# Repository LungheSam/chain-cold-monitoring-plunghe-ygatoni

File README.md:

# IoT-Based Cold Chain Monitoring for Vaccine Storage Units

CMU Africa · 04-645 A Internet of Things · Fall 2026
Putshu Lunghe Samuel (plunghe) · Yves Dominique Gatoni (ygatoni)

A Raspberry Pi 4 node watches a vaccine fridge (+2 to +8 °C): internal and ambient temperature,
humidity, door and 12 V power. It raises a local alarm and an SMS, keeps a record of every
temperature excursion, and is exposed as a W3C **Web Thing**. A React dashboard shows live data,
history and analytics. Extension: keypad PIN, solenoid lock and a QR unlock page.

```
edge (Pi) ──MQTT/TLS──> EMQX Cloud ──> back end (Railway: Node.js, WoT TD, SSE) ──> Firestore
                                               │                                     │
                                               └──> Africa's Talking SMS              └──> dashboard (Railway: React)
```

See [docs/architecture.md](docs/architecture.md) for the full picture.

## Where it runs

| Part | Service | Guide |
|---|---|---|
| MQTT broker | EMQX Cloud Serverless (free, TLS 8883) | [docs/deploy-railway.md](docs/deploy-railway.md) step 1 |
| Back end | Railway (service 1, root `backend/`) | [docs/deploy-railway.md](docs/deploy-railway.md) |
| Dashboard + unlock page | Railway (service 2, root `frontend/`) | [docs/deploy-railway.md](docs/deploy-railway.md) |
| Database + sign-in | Firebase (Firestore + Authentication) | [docs/firebase-setup.md](docs/firebase-setup.md) |
| SMS | Africa's Talking | [backend/README.md](backend/README.md) |

Why these choices (and why not HiveMQ or Firebase Hosting): [docs/decisions.md](docs/decisions.md) D3, D4, D18.

## Repository layout

| Folder | Contents |
|---|---|
| [edge/](edge/) | Python firmware for the Pi (alarm logic, drivers, keypad and lock, mock mode, offline queue) |
| [backend/](backend/) | Node.js back end: MQTT ingest, Web Thing API, Firestore, SMS, local test broker |
| [frontend/](frontend/) | React dashboard (light/dark), QR unlock page, small server for Railway |
| [firebase/](firebase/) | Firestore security rules and indexes |
| [broker/](broker/) | Mosquitto configuration (Docker), kept as a fallback broker |
| [hardware/](hardware/) | Fritzing wiring list, FreeCAD enclosure, KiCad carrier PCB |
| [docs/](docs/) | Architecture, wiring, MQTT topics, Thing Description, data model, decisions, [components list](docs/components.md), [purchase request](docs/purchase-request.md) ([Excel](docs/purchase-request.xlsx)), [test plan](docs/test-plan.md), [demo script](docs/demo-script.md), [report pictures](docs/report-media.md) |

## Prerequisites

| Tool | For | Notes |
|---|---|---|
| Python 3.11+ | edge | on the Pi it comes with Raspberry Pi OS |
| Node.js 24 LTS | backend, frontend | |
| FreeCAD 1.1, KiCad 10, Fritzing | hardware | FreeCAD and KiCad are not on PATH (paths in docs/decisions.md) |

Docker is not needed: `npm run broker` gives a local MQTT broker for testing.

## Running it on a laptop

Secrets go in `.env` files that are never committed. Each part has a `.env.example` to copy:
`backend/.env`, `edge/.env`, `frontend/.env.local`.

**First time:**

```bash
cd backend && npm install && npm test
cd ../frontend && npm install && npm test
cd ../edge && python -m venv .venv && .venv/Scripts/pip install -r requirements.txt && .venv/Scripts/python -m pytest
```

**Without any account** (memory store, local broker, demo dashboard):

```bash
cd backend && npm run broker       # terminal 1: local MQTT broker
cd backend && npm run dev          # terminal 2: back end (STORE=memory, DEV_AUTH=1 in backend/.env)
cd edge && .venv/Scripts/python -m coldchain.node    # terminal 3: simulated fridge (type `help`)
cd frontend && npm run demo        # terminal 4: dashboard with a generated week of data
```

**With the real services** (Firebase, EMQX: `backend/.env`, `edge/.env` and `frontend/.env.local` filled in):

```bash
cd backend && npm run check        # tests both MQTT logins and Firestore, prints no secrets
cd backend && npm run dev          # http://localhost:8080
cd edge && .venv/Scripts/python -m coldchain.node
cd frontend && npm run dev         # http://localhost:5173
```

In the node's terminal, `temp 9.5` makes the fridge too warm: WARNING at once, ALARM after 20 s.
More: [edge/README.md](edge/README.md), [backend/README.md](backend/README.md), [frontend/README.md](frontend/README.md).
On the Pi: [edge/SETUP.md](edge/SETUP.md).

**Whole chain in one command** (in-process broker + back end + simulated node, 34 checks):

```bash
cd backend && npm run e2e
```

## Project phases

| Phase | Content | Status |
|---|---|---|
| 0 | Plan and skeleton | done |
| 1 | Alarm logic + simulator | done |
| 2 | Real edge drivers, bring-up, Fritzing wiring list | done (not yet run on the Pi) |
| 3 | Back end (MQTT, Firestore, WoT, SMS, auth) | done, running against the real Firestore and EMQX |
| 4 | Dashboard + seed data | done, running against Firebase; light and dark themes |
| 5 | Keypad, lock, QR unlock | done (mock keypad and lock; not yet on the Pi) |
| 6 | FreeCAD enclosure | done (script runs headless, all parts valid; dimensions to VERIFY before printing) |
| 7 | KiCad carrier PCB | done (ERC/DRC clean, Gerbers ready; header position and parts to VERIFY before ordering) |
| 8 | End-to-end tests and demo script | done (`npm run e2e`: 34/34; system tests on the Pi to do, see docs/test-plan.md) |

Next: deploy on Railway ([docs/deploy-railway.md](docs/deploy-railway.md)), then the Pi bring-up.

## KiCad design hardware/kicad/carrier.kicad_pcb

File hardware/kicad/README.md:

# Carrier PCB (KiCad 10)

A 2-layer board the size of a Raspberry Pi HAT (65 × 56.5 mm) that plugs onto the Pi's 40-pin header
and replaces the breadboard wiring of `docs/wiring.md`. It is fully generated by scripts from one
table, checked by KiCad, and exported ready to order.

```bash
cd hardware/kicad
./build.sh          # about 2.5 minutes; needs KiCad 10 (its own Python and kicad-cli)
```

| File | What it does |
|---|---|
| `carrier.py` | **The netlist table**: every part, value, footprint and the net of each pin. Change the circuit here. |
| `make_schematic.py` | Writes `carrier.kicad_sch`: symbols copied from KiCad's library, a net label on every pin, functional blocks |
| `make_pcb.py` | Writes `carrier.kicad_pcb`: placement table, board outline, routing, GND pour on both layers, silkscreen labels |
| `router.py` | Small A* maze router (KiCad has no autorouter, and Freerouting needs Java) |
| `carrier.kicad_dru` | Extra design rules: lock tracks at least 1.0 mm |
| `build.sh` | Runs everything: ERC, routing, DRC (with schematic parity), exports |
| `output/` | Schematic PDF, ERC/DRC reports, `carrier-gerbers.zip` (Gerbers + drill), BOM, pick-and-place, STEP, renders |

The `.kicad_sch` and `.kicad_pcb` open normally in KiCad. If you edit them by hand, the next
`./build.sh` overwrites them: make the change in `carrier.py` or the placement table instead.

## Checks (last build)

- ERC: 0 errors, 0 warnings.
- DRC: 0 errors, 0 unconnected pads, schematic parity OK (every footprint, value and net matches the
  schematic). 5 warnings, all silkscreen text touching other silkscreen.

## What is on the board

| Block | Parts | Notes |
|---|---|---|
| Pi header | J1 2×20 female socket on the **bottom** side | Pin 1 = square pad, matches the Pi when the board sits on top |
| DS18B20 | J2 (JST-XH 3), R1 4.7 kΩ to 3.3 V | 1-Wire pull-up |
| DHT22 | J3 (JST-XH 3), R2 10 kΩ | leave R2 out if the DHT22 module has its own pull-up (VERIFY) |
| Reed switch | J4 (JST-XH 2) | uses the Pi's internal pull-up |
| 12 V sense | J9 (screw), R3 10 kΩ / R4 2.7 kΩ divider, C1 100 nF, R5 1 kΩ, D1 BAT54S | 2.55 V at 12 V, 3.19 V at 15 V; BAT54S clamps GPIO 22 between GND and 3.3 V |
| Buzzer | J6, R6 1 kΩ, Q1 BC547, D2 1N4148 | low-side switch, diode across the coil |
| LEDs | J5, R7/R8 330 Ω | LEDs sit on the lid; common GND |
| Lock | J10 (5 V lock adapter in), J11 (solenoid), Q2 AO3400A, R9 100 Ω, R10 10 kΩ, D3 1N4007 | R10 holds the gate low, so the lock is OFF when the Pi is off or booting |
| LCD level shifter | Q3/Q4 BSS138, R11/R12 10 kΩ to 5 V, J7 (JST-XH 4, backpack order GND 5V SDA SCL) | the 3.3 V side uses the Pi's own 1.8 kΩ pull-ups |
| Keypad, spare | J8 (1×8 header), J12 (GPIO 26 + GND) | |

Refs match the breadboard parts list in `docs/wiring.md` where the part is the same.
Differences from the breadboard, and why:

- **Q2 is an AO3400A (SOT-23)** instead of the IRLB8721 (TO-220). It is fully on at 3.3 V gate drive
  (R_DS(on) below 50 mΩ at 2.5 V, datasheet), so at about 1 A it dissipates about 50 mW. The TO-220 laid flat
  would need 21 × 11 mm of board.
- **D1 is a BAT54S** (two Schottky diodes in one package) instead of a single 1N5819: it clamps
  both above 3.3 V and below GND.
- **The BSS138 level shifter is on the board** instead of the separate module (D13).

### Why no PC817 optocoupler on the 12 V sense input

An optocoupler isolates two circuits with different grounds. Here the 12 V adapter's negative
must already be joined to the Pi's GND: the lock and the sense divider need a common ground anyway.
So isolation would gain nothing, and the divider + series resistor + clamp is simpler and protects
the GPIO against the realistic faults (a 15 V unloaded adapter, spikes, reversed or missing
ground on the sense wire). A PC817 would be the right choice only if the sensed supply had its own
ground, for example a separate battery system. It would then work like this: 12 V → resistor →
PC817 LED, and the photo-transistor pulls GPIO 22 low against a pull-up, so the logic is inverted.
Nothing on this board ever connects to 230 V.

### Track widths

| Nets | Width | Why |
|---|---|---|
| `+5V_LOCK`, `LOCK_N`, lock return (J10 GND ↔ Q2) | 1.0 mm | solenoid current about 1 A (VERIFY). IPC-2221 for 1 oz outer copper and a 10 °C rise needs 0.30 mm; 1.0 mm leaves margin for the pull-in surge |
| `+5V` | 0.4 mm | buzzer, LCD backlight (well under 0.5 A) |
| `+3V3`, `GND` tracks | 0.3 mm | plus a GND pour on both layers |
| signals | 0.25 mm | |

The Peltier's 12 V / ~5 A never comes onto this board: J9 carries only the divider's ~1 mA.

## Ordering

Upload `output/carrier-gerbers.zip` to any 2-layer PCB service (for example JLCPCB, PCBWay):
1.6 mm FR-4, 1 oz copper, HASL or ENIG, any colour. The design uses 0.25 mm tracks, 0.2 mm
clearance and 0.3 mm via drills, which every standard process allows. `output/carrier-bom.csv`
lists the parts and `output/carrier-pos.csv` the SMD positions (origin: bottom-left corner).

Shipping from abroad will not arrive before the 2 Dec demo (decisions.md), so the demo uses the
breadboard/protoboard build and this design is shown in the report.

## Before ordering: VERIFY

- [ ] Pi header position and pin 1 (from the HAT drawing: rows 2.23 / 4.77 mm from the top edge,
      pin 1 at x = 8.37 mm): print `output/carrier-top.png` at 1:1 or check the PDF against the Pi
- [ ] Standoff height between Pi and board: about 11 mm for an 8.5 mm female socket (measure the socket)
- [ ] BC547 pin order C-B-E (the footprint uses this order)
- [x] Keypad ribbon order R1–R4, C1–C4 matches J8 pins 1–8 (seller's diagram)
- [ ] LCD backpack pull-ups: if it already has 5 V pull-ups, leave out R11/R12
- [ ] DHT22 module pull-up: if it has one, leave out R2
- [ ] Solenoid current (measure): if it is above 1.5 A, ask for wider tracks

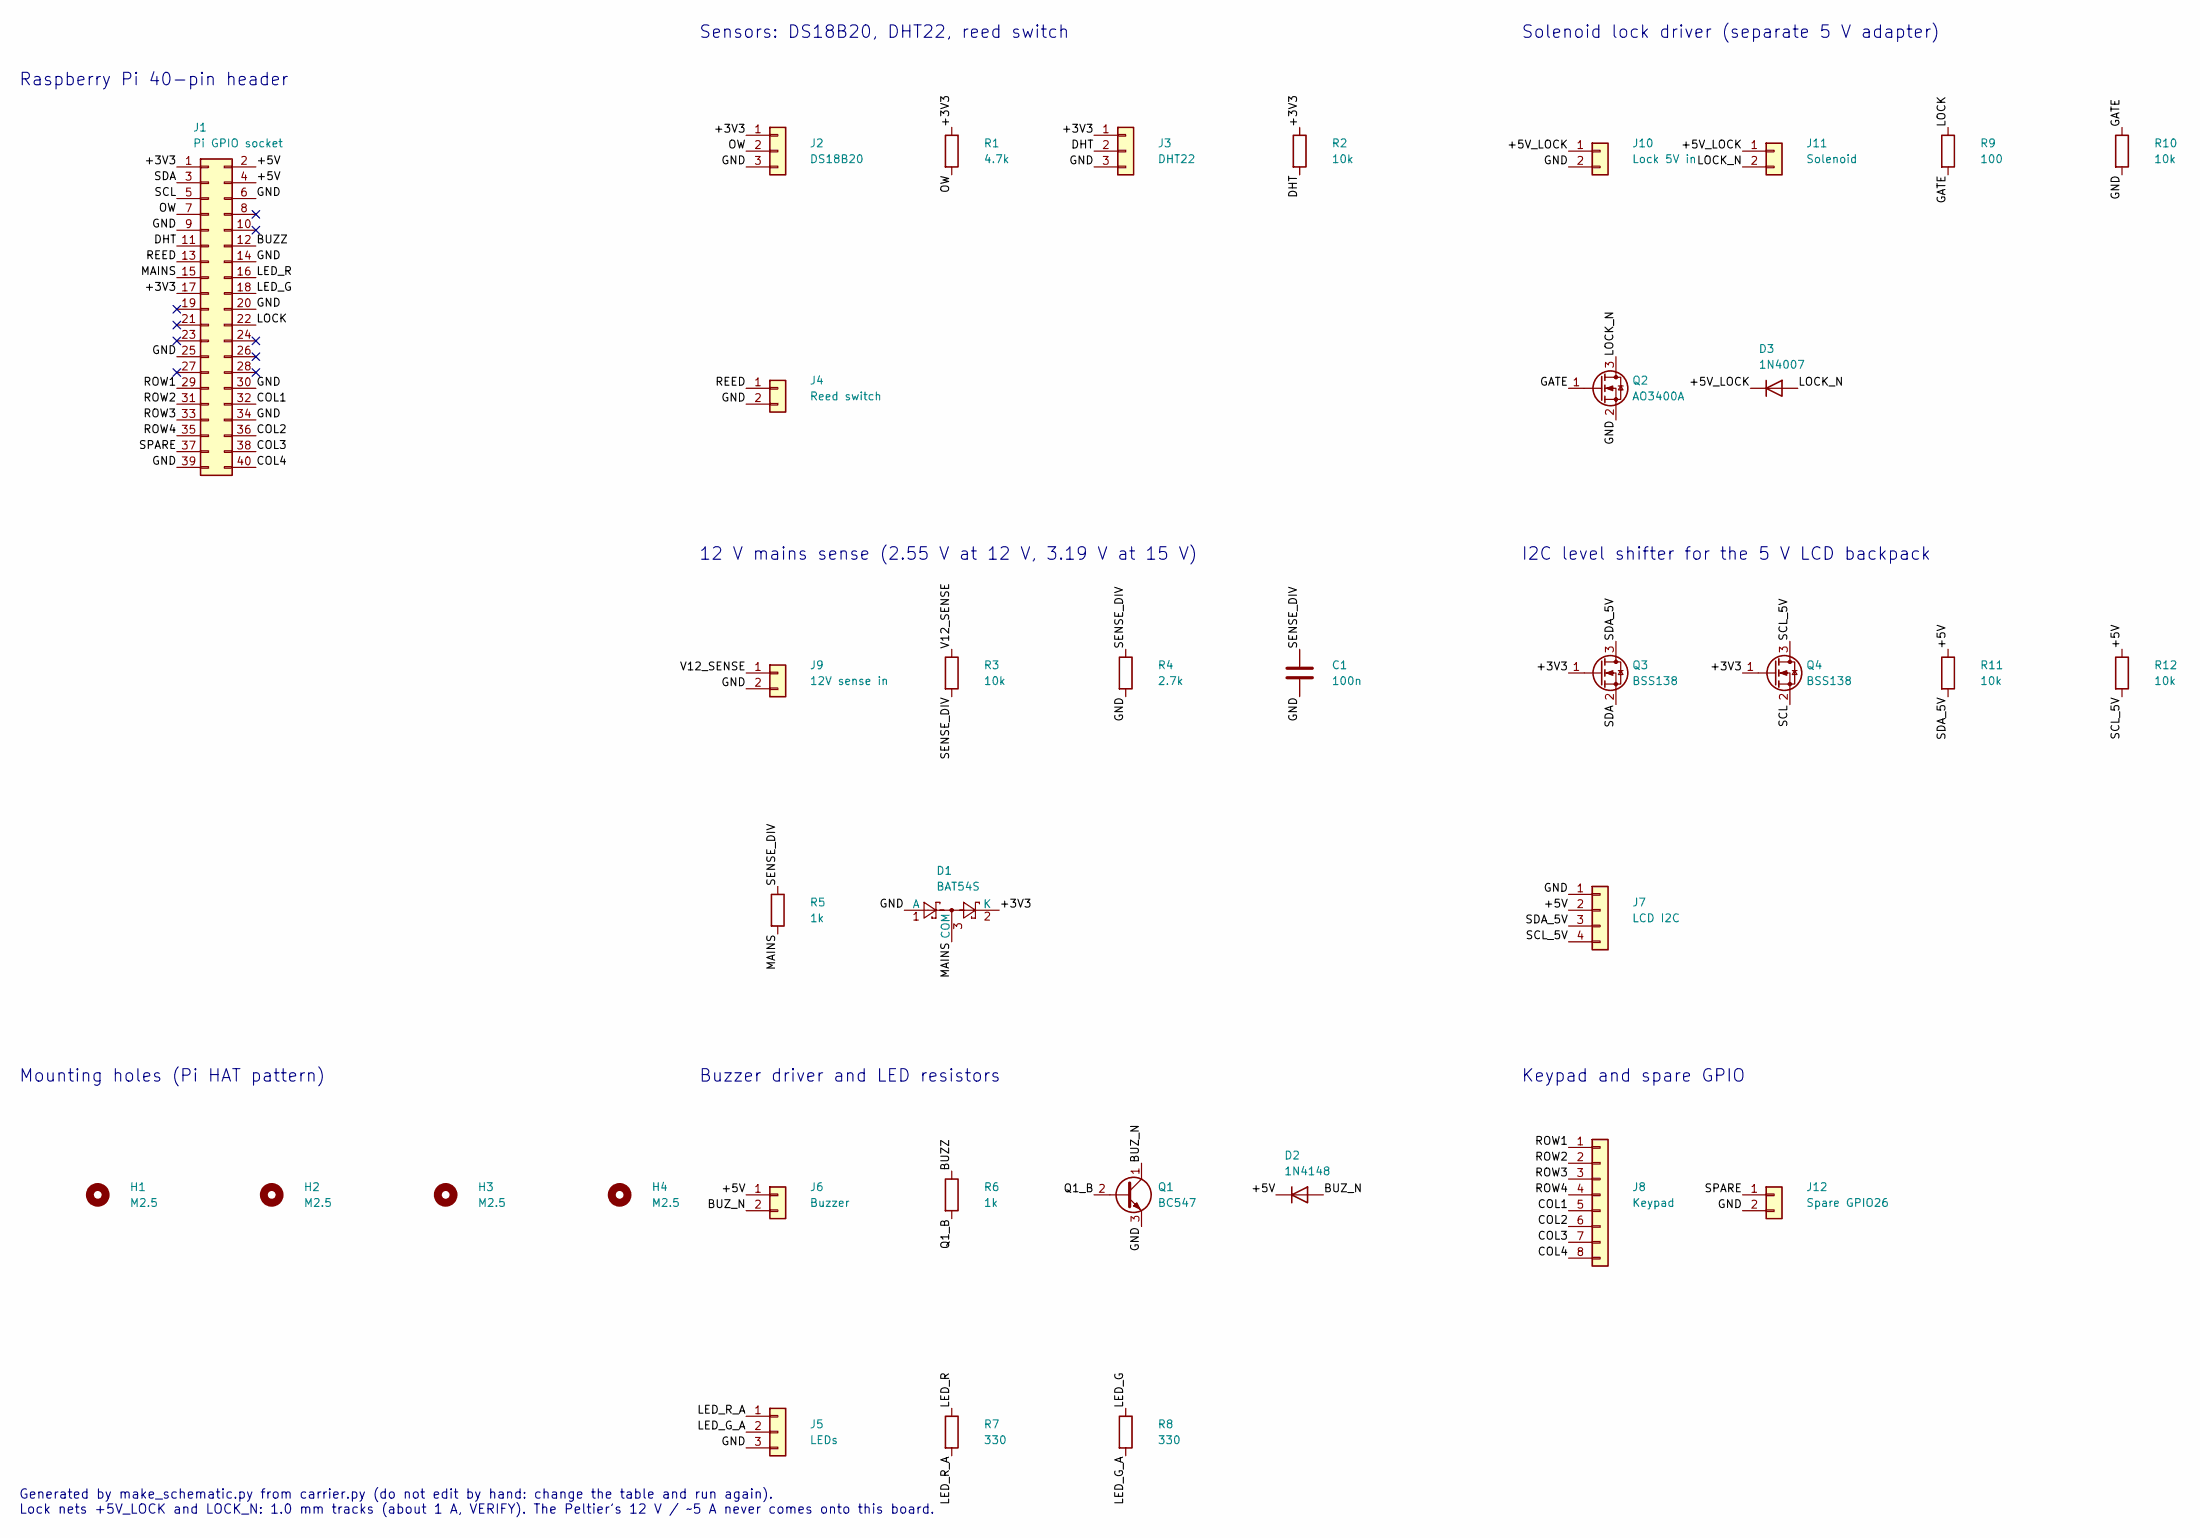
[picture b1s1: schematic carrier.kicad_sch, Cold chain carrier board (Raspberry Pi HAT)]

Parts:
C1: 100n; C_Disc_D5.0mm_W2.5mm_P5.00mm
D1: BAT54S; SOT-23
D2: 1N4148; D_DO-35_SOD27_P7.62mm_Horizontal
D3: 1N4007; D_DO-41_SOD81_P10.16mm_Horizontal
H1, H2, H3, H4: M2.5; MountingHole_2.7mm_M2.5
J1: Pi GPIO socket; PinSocket_2x20_P2.54mm_Vertical
J2: DS18B20; JST_XH_B3B-XH-A_1x03_P2.50mm_Vertical
J3: DHT22; JST_XH_B3B-XH-A_1x03_P2.50mm_Vertical
J4: Reed switch; JST_XH_B2B-XH-A_1x02_P2.50mm_Vertical
J5: LEDs; JST_XH_B3B-XH-A_1x03_P2.50mm_Vertical
J6: Buzzer; JST_XH_B2B-XH-A_1x02_P2.50mm_Vertical
J7: LCD I2C; JST_XH_B4B-XH-A_1x04_P2.50mm_Vertical
J8: Keypad; PinHeader_1x08_P2.54mm_Vertical
J9: 12V sense in; TerminalBlock_Phoenix_MKDS-1,5-2-5.08_1x02_P5.08mm_Horizont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
J10: Lock 5V in; TerminalBlock_Phoenix_MKDS-1,5-2-5.08_1x02_P5.08mm_Horizont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
J11: Solenoid; TerminalBlock_Phoenix_MKDS-1,5-2-5.08_1x02_P5.08mm_Horizont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
J12: Spare GPIO26; PinHeader_1x02_P2.54mm_Vertical
Q1: BC547; TO-92_Inline
Q2: AO3400A; SOT-23
Q3, Q4: BSS138; SOT-23
R1: 4.7k; R_Axial_DIN0207_L6.3mm_D2.5mm_P7.62mm_Horizontal
R2, R3, R10, R11, R12: 10k; R_Axial_DIN0207_L6.3mm_D2.5mm_P7.62mm_Horizontal
R4: 2.7k; R_Axial_DIN0207_L6.3mm_D2.5mm_P7.62mm_Horizontal
R5, R6: 1k; R_Axial_DIN0207_L6.3mm_D2.5mm_P7.62mm_Horizontal
R7, R8: 330; R_Axial_DIN0207_L6.3mm_D2.5mm_P7.62mm_Horizontal
R9: 100; R_Axial_DIN0207_L6.3mm_D2.5mm_P7.62mm_Horizontal

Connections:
/+3V3: D1.2 (K), J1.1, J1.17, J2.1, J3.1, Q3.1 (G), Q4.1 (G), R1.1, R2.1
/+5V: D2.1 (K), J1.2, J1.4, J6.1, J7.2, R11.1, R12.1
/+5V_LOCK: D3.1 (K), J10.1, J11.1
/BUZZ: J1.12, R6.1
/BUZ_N: D2.2 (A), J6.2, Q1.1 (C)
/COL1: J1.32, J8.5
/COL2: J1.36, J8.6
/COL3: J1.38, J8.7
/COL4: J1.40, J8.8
/DHT: J1.11, J3.2, R2.2
/GATE: Q2.1 (G), R9.2, R10.1
/GND: C1.2, D1.1 (A), J1.6, J1.9, J1.14, J1.20, J1.25, J1.30, J1.34, J1.39, J2.3, J3.3, J4.2, J5.3, J7.1, J9.2, J10.2, J12.2, Q1.3 (E), Q2.2 (S), R4.2, R10.2
/LED_G: J1.18, R8.1
/LED_G_A: J5.2, R8.2
/LED_R: J1.16, R7.1
/LED_R_A: J5.1, R7.2
/LOCK: J1.22, R9.1
/LOCK_N: D3.2 (A), J11.2, Q2.3 (D)
/MAINS: D1.3 (COM), J1.15, R5.2
/OW: J1.7, J2.2, R1.2
/Q1_B: Q1.2 (B), R6.2
/REED: J1.13, J4.1
/ROW1: J1.29, J8.1
/ROW2: J1.31, J8.2
/ROW3: J1.33, J8.3
/ROW4: J1.35, J8.4
/SCL: J1.5, Q4.2 (S)
/SCL_5V: J7.4, Q4.3 (D), R12.2
/SDA: J1.3, Q3.2 (S)
/SDA_5V: J7.3, Q3.3 (D), R11.2
/SENSE_DIV: C1.1, R3.2, R4.1, R5.1
/SPARE: J1.37, J12.1
/V12_SENSE: J9.1, R3.1

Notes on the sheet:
Raspberry Pi 40-pin header
Sensors: DS18B20, DHT22, reed switch
12 V mains sense (2.55 V at 12 V, 3.19 V at 15 V)
Buzzer driver and LED resistors
Solenoid lock driver (separate 5 V adapter)
I2C level shifter for the 5 V LCD backpack
Keypad and spare GPIO
Mounting holes (Pi HAT pattern)
Generated by make_schematic.py from carrier.py (do not edit by hand: change the table and run again). Lock nets +5V_LOCK and LOCK_N: 1.0 mm tracks (about 1 A, VERIFY). The Peltier's 12 V / ~5 A never comes onto this board.

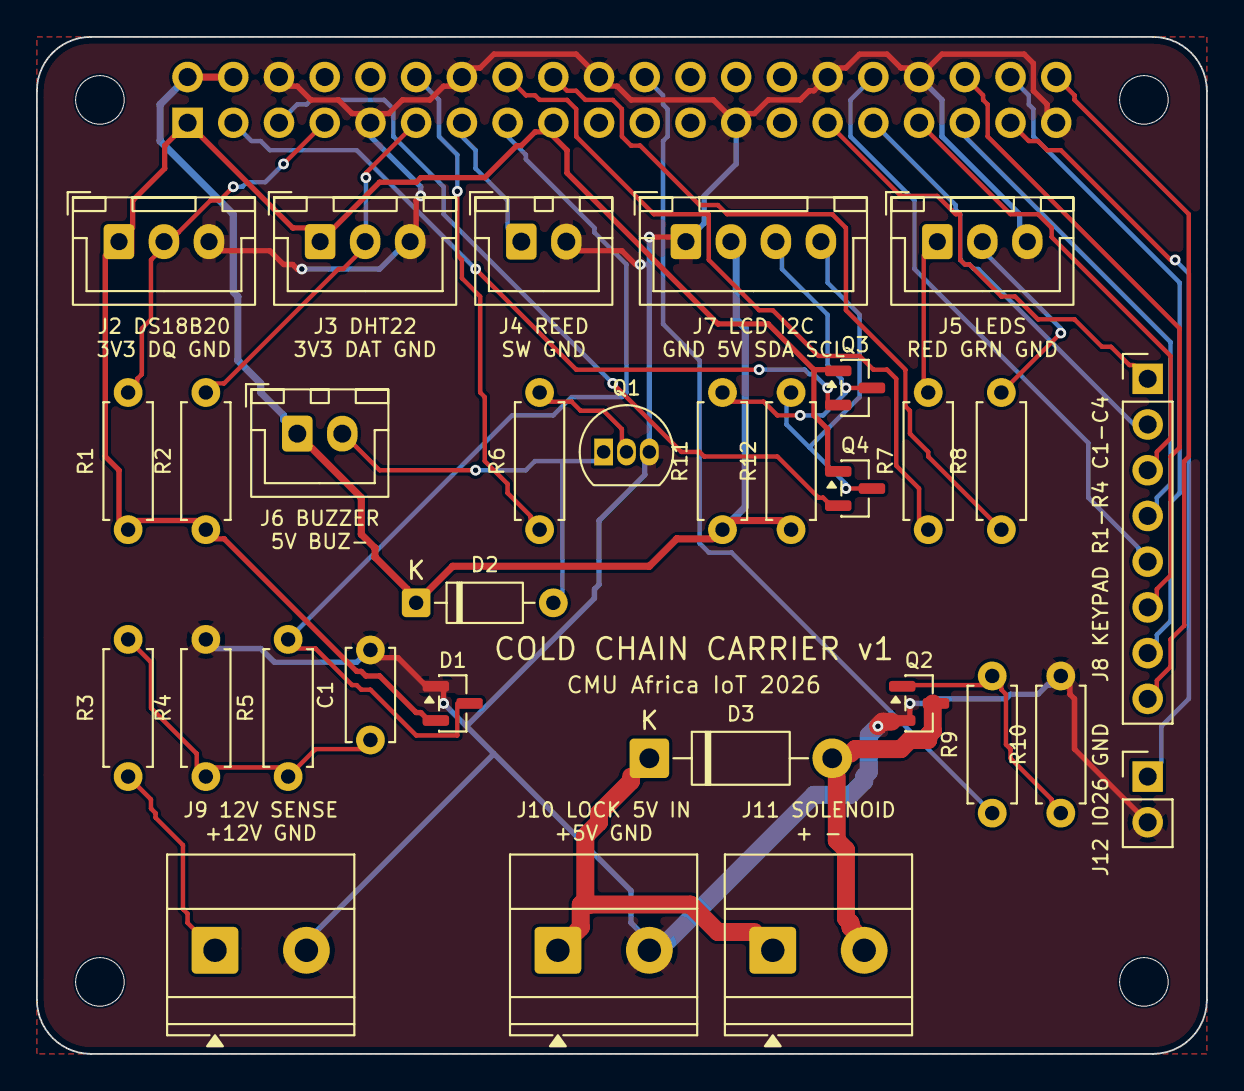
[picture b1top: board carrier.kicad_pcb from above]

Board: 2 copper layers, 65.0 x 56.5 mm, 36 parts (1 on the bottom side), 33 nets.

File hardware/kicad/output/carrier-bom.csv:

"Refs","Value","Footprint","Qty","Notes"
"C1","100n","Capacitor_THT:C_Disc_D5.0mm_W2.5mm_P5.00mm","1","filters noise on the sense line"
"D1","BAT54S","Package_TO_SOT_SMD:SOT-23","1","clamps GPIO 22 between GND and 3.3 V"
"D2","1N4148","Diode_THT:D_DO-35_SOD27_P7.62mm_Horizontal","1","across the buzzer coil"
"D3","1N4007","Diode_THT:D_DO-41_SOD81_P10.16mm_Horizontal","1","flyback diode across the solenoid"
"J1","Pi GPIO socket","Connector_PinSocket_2.54mm:PinSocket_2x20_P2.54mm_Vertical","1","2x20 female socket on the bottom side"
"J2","DS18B20","Connector_JST:JST_XH_B3B-XH-A_1x03_P2.50mm_Vertical","1",""
"J3","DHT22","Connector_JST:JST_XH_B3B-XH-A_1x03_P2.50mm_Vertical","1",""
"J4","Reed switch","Connector_JST:JST_XH_B2B-XH-A_1x02_P2.50mm_Vertical","1","uses the Pi's internal pull-up"
"J5","LEDs","Connector_JST:JST_XH_B3B-XH-A_1x03_P2.50mm_Vertical","1",""
"J6","Buzzer","Connector_JST:JST_XH_B2B-XH-A_1x02_P2.50mm_Vertical","1",""
"J7","LCD I2C","Connector_JST:JST_XH_B4B-XH-A_1x04_P2.50mm_Vertical","1","same order as the PCF8574 backpack"
"J8","Keypad","Connector_PinHeader_2.54mm:PinHeader_1x08_P2.54mm_Vertical","1","ribbon R1 R2 R3 R4 C1 C2 C3 C4, left to right with the keys facing you"
"J9","12V sense in","TerminalBlock_Phoenix:TerminalBlock_Phoenix_MKDS-1,5-2-5.08_1x02_P5.08mm_Horizontal","1","only the divider's ~1 mA; never the Peltier current"
"J10","Lock 5V in","TerminalBlock_Phoenix:TerminalBlock_Phoenix_MKDS-1,5-2-5.08_1x02_P5.08mm_Horizontal","1","separate 5 V 2 A adapter; its GND joins the Pi GND here"
"J11","Solenoid","TerminalBlock_Phoenix:TerminalBlock_Phoenix_MKDS-1,5-2-5.08_1x02_P5.08mm_Horizontal","1",""
"J12","Spare GPIO26","Connector_PinHeader_2.54mm:PinHeader_1x02_P2.54mm_Vertical","1",""
"Q1","BC547","Package_TO_SOT_THT:TO-92_Inline","1","C-B-E pin order (VERIFY on the part)"
"Q2","AO3400A","Package_TO_SOT_SMD:SOT-23","1","logic-level at 3.3 V, 5.7 A; the breadboard uses an IRLB8721 instead (docs/wiring.md)"
"Q3,Q4","BSS138","Package_TO_SOT_SMD:SOT-23","2",""
"R1","4.7k","Resistor_THT:R_Axial_DIN0207_L6.3mm_D2.5mm_P7.62mm_Horizontal","1","1-Wire pull-up"
"R2,R3,R10,R11,R12","10k","Resistor_THT:R_Axial_DIN0207_L6.3mm_D2.5mm_P7.62mm_Horizontal","5","5 V side pull-up; the 3.3 V side uses the Pi's own 1.8k pull-ups,DHT22 pull-up; leave out if the module has one (VERIFY),keeps the lock OFF when the Pi is off"
"R4","2.7k","Resistor_THT:R_Axial_DIN0207_L6.3mm_D2.5mm_P7.62mm_Horizontal","1",""
"R5,R6","1k","Resistor_THT:R_Axial_DIN0207_L6.3mm_D2.5mm_P7.62mm_Horizontal","2","limits the clamp current"
"R7,R8","330","Resistor_THT:R_Axial_DIN0207_L6.3mm_D2.5mm_P7.62mm_Horizontal","2","green LED,red LED"
"R9","100","Resistor_THT:R_Axial_DIN0207_L6.3mm_D2.5mm_P7.62mm_Horizontal","1","gate series resistor"

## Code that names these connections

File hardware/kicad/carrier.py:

"""The carrier board as a table: every part, its value, footprint and which net each pin is on.

make_schematic.py and make_pcb.py both read this table, so the schematic and the board can never
disagree (and `kicad-cli pcb drc --schematic-parity` checks it again).

Circuit decisions are in docs/wiring.md. Pin numbers of the Pi header are physical pin numbers.
"""

# ---------------------------------------------------------------- Raspberry Pi 40-pin header
# Physical pin -> net. Pins that are not listed are not used (no-connect flags in the schematic).
PI_PINS = {
    1: "+3V3", 17: "+3V3",
    2: "+5V", 4: "+5V",
    6: "GND", 9: "GND", 14: "GND", 20: "GND", 25: "GND", 30: "GND", 34: "GND", 39: "GND",
    3: "SDA",        # GPIO 2
    5: "SCL",        # GPIO 3
    7: "OW",         # GPIO 4   DS18B20 (1-Wire)
    11: "DHT",       # GPIO 17  DHT22
    12: "BUZZ",      # GPIO 18  buzzer (PWM)
    13: "REED",      # GPIO 27  door reed switch (internal pull-up)
    15: "MAINS",     # GPIO 22  12 V present (divider)
    16: "LED_R",     # GPIO 23
    18: "LED_G",     # GPIO 24
    22: "LOCK",      # GPIO 25  lock MOSFET gate (pulled down at boot)
    29: "ROW1", 31: "ROW2", 33: "ROW3", 35: "ROW4",   # GPIO 5, 6, 13, 19
    32: "COL1", 36: "COL2", 38: "COL3", 40: "COL4",   # GPIO 12, 16, 20, 21
    37: "SPARE",     # GPIO 26  kept free (e.g. a hardware acknowledge button)
}

# Footprint shortcuts
JST2 = "Connector_JST:JST_XH_B2B-XH-A_1x02_P2.50mm_Vertical"
JST3 = "Connector_JST:JST_XH_B3B-XH-A_1x03_P2.50mm_Vertical"
JST4 = "Connector_JST:JST_XH_B4B-XH-A_1x04_P2.50mm_Vertical"
SCREW2 = "TerminalBlock_Phoenix:TerminalBlock_Phoenix_MKDS-1,5-2-5.08_1x02_P5.08mm_Horizontal"
RES = "Resistor_THT:R_Axial_DIN0207_L6.3mm_D2.5mm_P7.62mm_Horizontal"

# ---------------------------------------------------------------- parts
# ref: (symbol, value, footprint, {pin number: net}, group, note)
PARTS = {
    "J1": ("Connector_Generic:Conn_02x20_Odd_Even", "Pi GPIO socket",
           "Connector_PinSocket_2.54mm:PinSocket_2x20_P2.54mm_Vertical",
           {str(p): n for p, n in PI_PINS.items()}, "pi", "2x20 female socket on the bottom side"),

    # Sensors
    "J2": ("Connector_Generic:Conn_01x03", "DS18B20", JST3, {"1": "+3V3", "2": "OW", "3": "GND"}, "sensors", ""),
    "R1": ("Device:R", "4.7k", RES, {"1": "+3V3", "2": "OW"}, "sensors", "1-Wire pull-up"),
    "J3": ("Connector_Generic:Conn_01x03", "DHT22", JST3, {"1": "+3V3", "2": "DHT", "3": "GND"}, "sensors", ""),
    "R2": ("Device:R", "10k", RES, {"1": "+3V3", "2": "DHT"}, "sensors",
           "DHT22 pull-up; leave out if the module has one (VERIFY)"),
    "J4": ("Connector_Generic:Conn_01x02", "Reed switch", JST2, {"1": "REED", "2": "GND"}, "sensors",
           "uses the Pi's internal pull-up"),

    # 12 V mains sense: 10k / 2.7k divider (2.55 V at 12 V), RC filter, 1k series, BAT54S clamp
    "J9": ("Connector_Generic:Conn_01x02", "12V sense in", SCREW2, {"1": "V12_SENSE", "2": "GND"}, "mains",
           "only the divider's ~1 mA; never the Peltier current"),
    "R3": ("Device:R", "10k", RES, {"1": "V12_SENSE", "2": "SENSE_DIV"}, "mains", ""),
    "R4": ("Device:R", "2.7k", RES, {"1": "SENSE_DIV", "2": "GND"}, "mains", ""),
    "C1": ("Device:C", "100n", "Capacitor_THT:C_Disc_D5.0mm_W2.5mm_P5.00mm",
           {"1": "SENSE_DIV", "2": "GND"}, "mains", "filters noise on the sense line"),
    "R5": ("Device:R", "1k", RES, {"1": "SENSE_DIV", "2": "MAINS"}, "mains", "limits the clamp current"),
    "D1": ("Diode:BAT54S", "BAT54S", "Package_TO_SOT_SMD:SOT-23",
           {"1": "GND", "2": "+3V3", "3": "MAINS"}, "mains", "clamps GPIO 22 between GND and 3.3 V"),

    # Buzzer (NPN low-side) and LED resistors
    "J6": ("Connector_Generic:Conn_01x02", "Buzzer", JST2, {"1": "+5V", "2": "BUZ_N"}, "outputs", ""),
    "R6": ("Device:R", "1k", RES, {"1": "BUZZ", "2": "Q1_B"}, "outputs", ""),
    "Q1": ("Transistor_BJT:BC547", "BC547", "Package_TO_SOT_THT:TO-92_Inline",
           {"1": "BUZ_N", "2": "Q1_B", "3": "GND"}, "outputs", "C-B-E pin order (VERIFY on the part)"),
    "D2": ("Diode:1N4148", "1N4148", "Diode_THT:D_DO-35_SOD27_P7.62mm_Horizontal",
           {"1": "+5V", "2": "BUZ_N"}, "outputs", "across the buzzer coil"),
    "J5": ("Connector_Generic:Conn_01x03", "LEDs", JST3, {"1": "LED_R_A", "2": "LED_G_A", "3": "GND"}, "outputs", ""),
    "R7": ("Device:R", "330", RES, {"1": "LED_R", "2": "LED_R_A"}, "outputs", "red LED"),
    "R8": ("Device:R", "330", RES, {"1": "LED_G", "2": "LED_G_A"}, "outputs", "green LED"),

    # Solenoid lock: logic-level MOSFET low-side switch, own 5 V adapter
    "J10": ("Connector_Generic:Conn_01x02", "Lock 5V in", SCREW2, {"1": "+5V_LOCK", "2": "GND"}, "lock",
            "separate 5 V 2 A adapter; its GND joins the Pi GND here"),
    "J11": ("Connector_Generic:Conn_01x02", "Solenoid", SCREW2, {"1": "+5V_LOCK", "2": "LOCK_N"}, "lock", ""),
    "R9": ("Device:R", "100", RES, {"1": "LOCK", "2": "GATE"}, "lock", "gate series resistor"),
    "R10": ("Device:R", "10k", RES, {"1": "GATE", "2": "GND"}, "lock", "keeps the lock OFF when the Pi is off"),
    "Q2": ("Transistor_FET:AO3400A", "AO3400A", "Package_TO_SOT_SMD:SOT-23",
           {"1": "GATE", "2": "GND", "3": "LOCK_N"}, "lock",
           "logic-level at 3.3 V, 5.7 A; the breadboard uses an IRLB8721 instead (docs/wiring.md)"),
    "D3": ("Diode:1N4007", "1N4007", "Diode_THT:D_DO-41_SOD81_P10.16mm_Horizontal",
           {"1": "+5V_LOCK", "2": "LOCK_N"}, "lock", "flyback diode across the solenoid"),

    # I2C level shifter for the 5 V LCD backpack (two BSS138, docs/wiring.md D13)
    "Q3": ("Transistor_FET:BSS138", "BSS138", "Package_TO_SOT_SMD:SOT-23",
           {"1": "+3V3", "2": "SDA", "3": "SDA_5V"}, "i2c", ""),
    "Q4": ("Transistor_FET:BSS138", "BSS138", "Package_TO_SOT_SMD:SOT-23",
           {"1": "+3V3", "2": "SCL", "3": "SCL_5V"}, "i2c", ""),
    "R11": ("Device:R", "10k", RES, {"1": "+5V", "2": "SDA_5V"}, "i2c",
            "5 V side pull-up; the 3.3 V side uses the Pi's own 1.8k pull-ups"),
    "R12": ("Device:R", "10k", RES, {"1": "+5V", "2": "SCL_5V"}, "i2c", ""),
    "J7": ("Connector_Generic:Conn_01x04", "LCD I2C", JST4,
           {"1": "GND", "2": "+5V", "3": "SDA_5V", "4": "SCL_5V"}, "i2c", "same order as the PCF8574 backpack"),

    # Keypad and spare
    "J8": ("Connector_Generic:Conn_01x08", "Keypad", "Connector_PinHeader_2.54mm:PinHeader_1x08_P2.54mm_Vertical",
           {"1": "ROW1", "2": "ROW2", "3": "ROW3", "4": "ROW4", "5": "COL1", "6": "COL2", "7": "COL3", "8": "COL4"},
           "keypad", "ribbon R1 R2 R3 R4 C1 C2 C3 C4, left to right with the keys facing you"),
    "J12": ("Connector_Generic:Conn_01x02", "Spare GPIO26", "Connector_PinHeader_2.54mm:PinHeader_1x02_P2.54mm_Vertical",
            {"1": "SPARE", "2": "GND"}, "keypad", ""),

    # Mounting holes on the HAT pattern (58 x 49 mm), M2.5
    **{"H%d" % k: ("Mechanical:MountingHole", "M2.5", "MountingHole:MountingHole_2.7mm_M2.5", {}, "mech",
                   "M2.5 spacer to the Pi") for k in range(1, 5)},
}

GROUP_TITLES = {
    "pi": "Raspberry Pi 40-pin header",
    "sensors": "Sensors: DS18B20, DHT22, reed switch",
    "mains": "12 V mains sense (2.55 V at 12 V, 3.19 V at 15 V)",
    "outputs": "Buzzer driver and LED resistors",
    "lock": "Solenoid lock driver (separate 5 V adapter)",
    "i2c": "I2C level shifter for the 5 V LCD backpack",
    "keypad": "Keypad and spare GPIO",
    "mech": "Mounting holes (Pi HAT pattern)",
}

# Nets that carry the lock current (~1 A, VERIFY): wide tracks, see make_pcb.py
POWER_NETS = {"+5V_LOCK": 1.0, "LOCK_N": 1.0, "+5V": 0.5, "GND": 0.5}


def nets():
    """net -> list of (ref, pin)."""
    result = {}
    for ref, (_, _, _, pins, _, _) in PARTS.items():
        for pin, net in pins.items():
            result.setdefault(net, []).append((ref, pin))
    return result


if __name__ == "__main__":
    for net, pins in sorted(nets().items()):
        print("%-10s %s" % (net, " ".join("%s.%s" % p for p in pins)))
